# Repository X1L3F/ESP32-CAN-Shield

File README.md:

# ESP32-CAN-Shield

## Overview

This ESP32-CAN-Shield is a custom-designed shield for the ESP32-S3, primarily used as a CAN (Controller Area Network) to WiFi bridge. It enables seamless integration and communication between CAN network systems and WiFi networks, making it ideal for automotive and industrial applications where remote monitoring and control are necessary. The developed ESP32-CAN Shieled can be deployed in two different use cases:

#### 1. Single Device CAN-WiFi Interface
   
One ESP32-CAN Shield is linked to a CAN device, such as an OBD2 unit in an automotive vehicle. The ESP32 generates its own WiFi network, to which the Connector is subsequently tethered.

#### 2. Multi-Device CAN-WiFi Network
Multiple ESP32-CAN Shields are each linked to their respective CAN devices, while all ESP32 devices are connected to an established WiFi network. The Connector actively monitors all CANeth messages transmitted over the WiFi network and directed towards it. This use case is also used for development and testing.

## Compatibility

**Note:** ESP32 development boards come in various widths. Ensure to adjust the header width of this shield to match your specific ESP32 board model.

## Hardware

The shield features a robust CAN transceiver schematic, including an optional termination resistor for network integrity.

### Key Components:

- **CAN Transceiver:** The [TCAN332DCNT](https://www.ti.com/lit/ds/symlink/tcan332.pdf?ts=1706343800000&ref_url=https%253A%252F%252Fwww.ti.com%252Fproduct%252FTCAN332%252Fpart-details%252FTCAN332D), a high-performance CAN transceiver from Texas Instruments.
- **Power Connection:** The shield connects directly to the ESP32 board via two header columns, supplying 3.3V power and ground.
- **Signal Pins:** Dedicated GPIOs for CAN high (CAN-H) and low (CAN-L) signals for RX and TX operations.
- **Termination Resistor:** A bridge connector enables an end-termination resistor, essential for reducing signal reflections on the CAN bus.
- **CAN Interface:** Utilizes a 2x5 IDC for CAN bus interfacing, with an IDC to D-SUB cable for standard D-SUB connections, compatible with devices like the Vector VN1610 and tools like CANoe.
- **Protection:** Incorporates a PESD2CAN diode in a small SOT23 SMD package, designed to protect the CAN lines from ESD and other transient damages. This ensures reliability and longevity in automotive environments.
- **Manufacturing Compatibility:** Designed in accordance with JLC Design Rules for easy custom manufacturing.

## Software

The software is structured into two components:

- The Gateway runs on the ESP and serves as the translater of CAN to caneth/caneth to CAN messages. It also serves a Website where different settings like CAN-speed and remote IP can be changed or a CAN-ID filter can be used.
- The Connector which runs on a PC and sends/receives/loggs CANeth Messages to the Gateway. It basically connects like Wireshark or any other tool.

### Installation

#### Gateway

The Gateway is developed with PlatformIO it can be installed as VScode [extension](https://marketplace.visualstudio.com/items?itemName=platformio.platformio-ide). When the Gateway folder is opened in VScode, PlatformIO is automatically initalized and the project can be compiled and uploaded to the ESP. Make sure to add a `Gateway/include/Secrets.h` file with the desired WIFI configuration.

```
#ifndef SECRETS_H
#define SECRETS_H

//Put in the SSID and Password of the WIFI
#define WIFI_SSID "own-WIFI-SSID"
#define WIFI_PASSWORD "own-WIFI-Password"

//Define the SSID and Password for the hotspot of the ESP32
#define Hotspot_SSID "own-ESP32-SSID"
#define Hotspot_PASSWORD "own-ESP32-Password"

#endif
```

In the main.cpp of the gateway, the network setting can be modified via the mode variable.

- Mode = 1: The ESP32 connects to a predefined network.
- Mode = 2: The ESP32 acts as a Wi-Fi Access Point, which one still needs to connect to with a computer.

```
...
// WiFi and Hotspot settings
//Make sure you adjust the ssid and password in your Secrets.h to your WIFI
//mode = 1: connection with a predefined WIFI
//mode = 2: ESP32 as a WLAN-Access-Point
int mode = 1;
...
```
#### Webserver
On the Webserver there are several options to configure the communications and apply filter.

CAN Configuration:
- Remote IP: Enter the IP, where the messages should be send to. (Look up the IPv4-Adresse of your computer.)
- CAN Bit Rate: Adjust the Bit Rate according to your settings

Filter Option:
- Allow all Messages: All messages are forwarded. You can add CAN-IDs to to the Blacklist to block messages from certain CAN-Devices.
- Block all Messages: Blocks all messages. You can add CAN-IDs to to the Whitelist to forward messages from certain CAN-Devices.

Restart: Restarts the ESP32. It can take a moment to reconnet to the WIFI or you have to connect to the Hotspot from the ESP32 again.

#### Connector

The backend of the Connector application `Connector/qt_application_backend.py` is a Python script with no external dependencies, besides the default Python 3.9 libraries. The programmed functions, classes, and their methods provide a comprehensive toolset to send, receive, and log CANeth messages. By default, the Connector is listening on all UDP IP channels for CANeth messages. Filters can be applied to restrict IPv4 addresses via a blacklist and whitelist. In addition to that, the CANeth messages can also be filtered by CAN ID via a blacklist and whitelist. The IPv4 address filter and the CAN ID filter are initially set to an empty blacklist, allowing all CANeth messages to be received. For ease of use, a graphical user interface (GUI) was implemented for the frontend of the Connector application `Connector/qt_application_frontend.py` using [PyQt5](https://pypi.org/project/PyQt5/). 

As depicted in the screenshot of the Connector application, the aforementioned features can be accessed through the GUI. In the popup of the advanced settings window, the UDP IP and the UDP port of the socket can be adjusted.

For independent usage of the Connector application outside of a Python interpreter, it was compiled with [PyInstaller](https://pypi.org/project/pyinstaller/) into a ConnectorApp.exe for [Windows 23H2](https://support.microsoft.com/de-de/topic/updateverlauf-von-windows-11-version-23h2-59875222-b990-4bd9-932f-91a5954de434). The .exe file is designed to support 1080p and 2k screen resolutions. A detailed guide for compiling an .exe-file with PyInstaller from a .py-PyQt5 file and .ui-PyQt5 file is provide under `dist/PyInstallerGuide`.

#### Simulation

To simulate a device that sends/receives CAN-messages to the Bus either CANoe or a python script found in `Tools/canDevice.py` is used with a Vector VN1610. To use it follow this steps:

- install the `pip install python-can` package
- install the [latest drivers](https://www.vector.com/int/en/support-downloads/download-center/#product=%5B%2256540%22%5D&downloadType=%5B%22drivers%22%5D&tab=1&pageSize=30&sort=date&order=desc) for the Vector hardware Interface
- install the [XL Driver Library](https://www.vector.com/int/en/support-downloads/download-center/#product=%5B%22175%22%5D&downloadType=%5B%22drivers%22%5D&tab=1&pageSize=15&sort=date&order=desc) and copy the `vxlapi64.dll` into the working directory (If the driver doesn't show up, you have to manually add the vxlapi64.dll file path to XL Driver Library)

### Usage

1. Attach CAN-Shield to ESP32 connect it to PC with the right USB-port and flash the Gateway-software. Before flashing, ensure you have included the [Secret.h](https://github.com/X1L3F/ESP32-CAN-Shield?tab=readme-ov-file#gateway) file in your project. Select your desired network mode in the `Gateway/main.cpp`.
2. Plug in IDC and connect to VN1610. Connect VN1610 to PC.
3. Access the web server using the IPv4-address of the ESP32. The method to retrieve this address depends on your network connection mode:
   - Hotspot on ESP32: Connect your computer to the ESP32's hotspot. Use the ipconfig command in your computer's command prompt to find the IPv4 address of the ESP32. Type this address into your web browser to access the web server.
   - Conncetion to predefined WIFI: The IPv4 address will be displayed in the Arduino IDE's Serial Monitor. Enter this IPv4 address into your web browser to navigate to the web server.
4. Configure the CAN Configurations on the [WebServer](https://github.com/X1L3F/ESP32-CAN-Shield?tab=readme-ov-file#webserver)
5. Start `Connector/qt_application_frontend.py` or the `dist/ConnectorApp.exe`, the UDP traffic can also be analyzed with Wireshark by filtering for `CANeth`
6. Start CANoe or `Tools/canDevice.py`

In the linked YouTube video a quick, visual introduction for the [Multi-Device CAN-WiFi Network](https://youtu.be/aGkZIFaZris) use case and how to use the Connector application is provided. The video summarizes the aforementioned steps for practical work with the code.

<div align="center">
  
</div>

## Additional resources for understanding CAN and programming CANeth
- [A Simple intro to CAN](https://www.csselectronics.com/pages/can-bus-simple-intro-tutorial)
- [ISO 11898](https://www.iso.org/standard/63648.html)
- [Two Wire Automotive Interface](https://docs.espressif.com/projects/esp-idf/en/latest/esp32s2/api-reference/peripherals/twai.html)

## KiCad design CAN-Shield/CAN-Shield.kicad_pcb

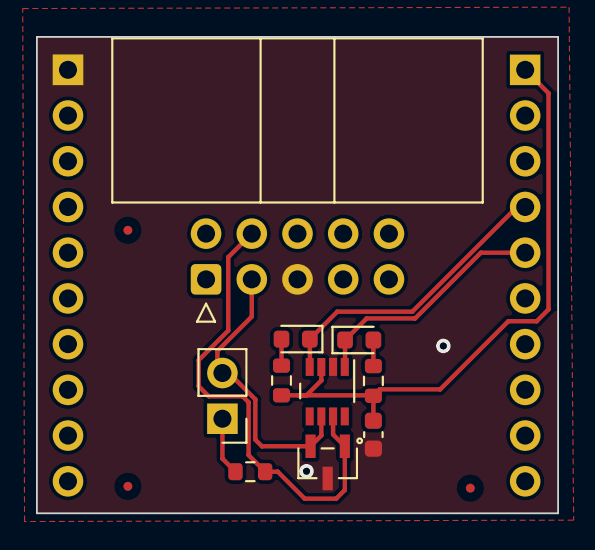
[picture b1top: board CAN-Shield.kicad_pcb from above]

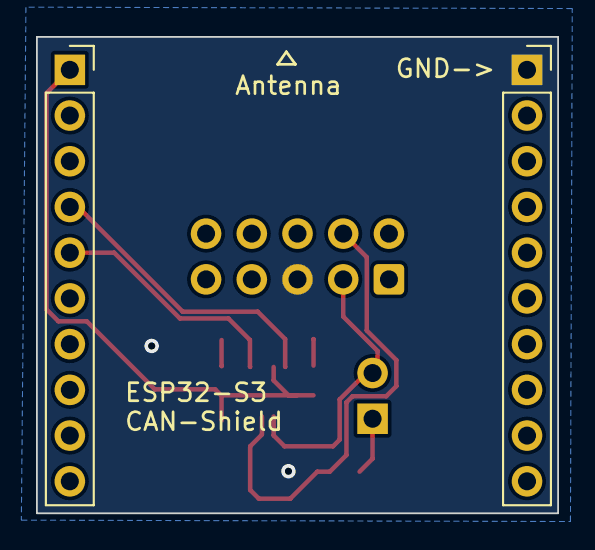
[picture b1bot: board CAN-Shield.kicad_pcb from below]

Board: 2 copper layers, 29.0 x 26.5 mm, 15 parts (2 on the bottom side), 9 nets.

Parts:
C1: 100nF; C_0603_1608Metric
FID1, FID2, FID3: Fiducial
J1, J2: Conn_01x10_Socket; PinSocket_1x10_P2.54mm_Vertical
J3: Conn_01x02_Pin; PinHeader_1x02_P2.54mm_Vertical
J6: Conn_02x05_Odd_Even; IDC-Header_2x05_P2.54mm_Horizontal
R1, R2: 390; R_0603_1608Metric
R3: 120; R_0603_1608Metric
RXCAN1: orange; LED_0603_1608Metric
TXCAN1: blue; LED_0603_1608Metric
U1: TCAN332GDCNT
U2: PESD2CAN

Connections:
+3.3V: C1.1, J2.1, R1.1, R2.1, U1.3 (VCC)
/CAN_H: J6.4, R3.1, U1.7 (CANH), U2.1 (K1)
/CAN_L: J3.2, J6.3, U1.6 (CANL), U2.2 (K2)
/CAN_RX: J2.4, RXCAN1.1 (K), U1.4 (RXD)
/CAN_TX: J2.5, TXCAN1.1 (K), U1.1 (TXD)
GND: C1.2, J1.1, J6.5, U1.2 (GND), U2.3 (DK)
unnamed: J3.1, R3.2
unnamed: R2.2, RXCAN1.2 (A)
unnamed: R1.2, TXCAN1.2 (A)

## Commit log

2023-12-01 init KiCAD with JLC rules
2023-12-01 add gitignore
2023-12-01 remove ignored files
2024-01-27 added final PCB
2024-01-27 updated Project Info
2024-02-09 initial Software
2024-02-11 software mvp
2024-02-11 added settings instructions
2024-02-14 added todo
2024-02-14 Anpassung WebServer
2024-02-16 Update for CanIDFilter. Changes to UdpCommunicator and WebServerManager
2024-02-19 Desgin of WebServer updated
2024-02-19 Build_2024_02_19
2024-02-19 Sim bla (#1)
2024-03-12 ESP32 als WlanAccesPoint
2024-03-21 connector class added
2024-03-21 added whitelist and blacklist for IPv4 addresses; testd
2024-03-22 message logger added and tested; canDevice improved; hex-string fixed
2024-03-22 message ID filter added
2024-03-22 Updated IP
2024-03-22 Gateway
2024-03-22 ESP to wifi
2024-03-22 Connector, MessageLogger, CanDevice modified (#3)
2024-03-22 Hotspot
2024-03-23 Mode Change
2024-03-23 connector modified; file removed
2024-03-24 Updated Filter and Webserver
2024-03-24 QT- live-view working, canDevice improved
2024-03-25 IPv4 adress filter works with hmi
2024-03-25 CAN-ID filter implemented
2024-03-25 Advanced Socket Settings Added
2024-03-26 Sending CAN messages added, visuals improved
2024-03-26 time stamp added, print statements removed, comments added
2024-03-26 Updated Filter and Webserver (#4)
2024-03-26 Qt application (#5)
    Added QT-Application
2024-03-26 ConnectorApp as .exe
2024-03-26 Update Webserver Design
2024-03-26 ConnectorApp layout improved
2024-03-26 Screenshot of the Connector Application
2024-03-26 File removed
2024-05-03 Add files via upload
    Added presentation
